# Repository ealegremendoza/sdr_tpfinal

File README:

TENSIOMETRO DIGITAL
TP Final de la materia Sistemas de Representación R1032 UTN FRBA.

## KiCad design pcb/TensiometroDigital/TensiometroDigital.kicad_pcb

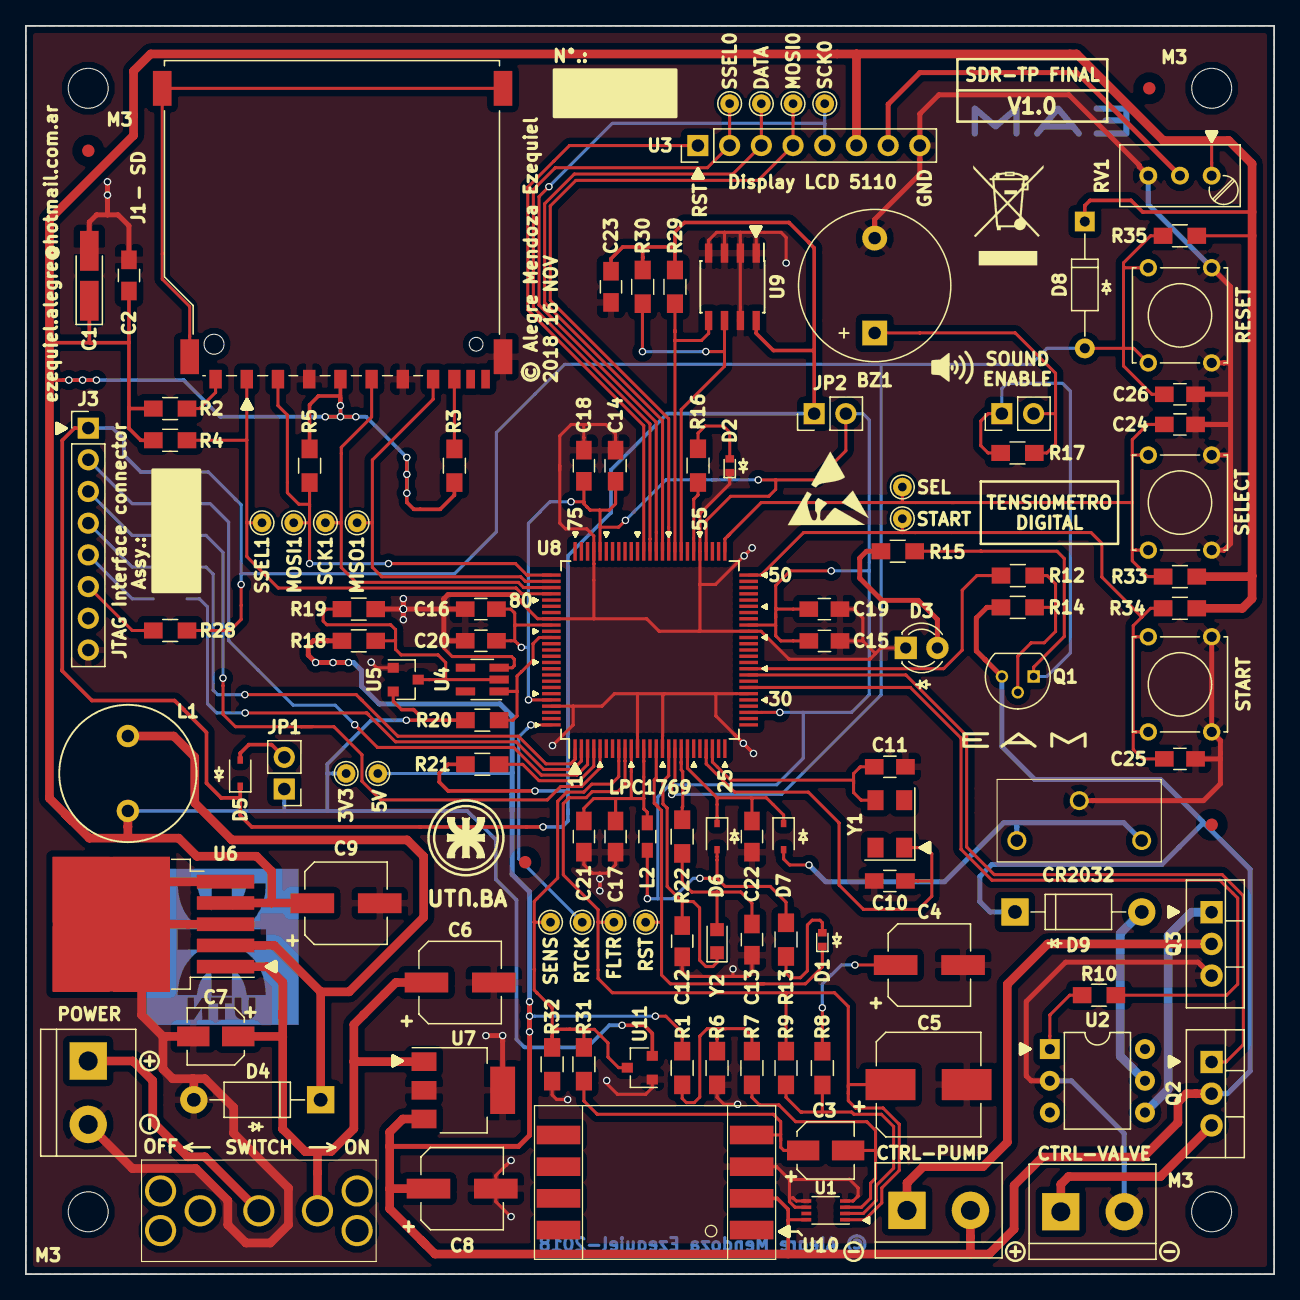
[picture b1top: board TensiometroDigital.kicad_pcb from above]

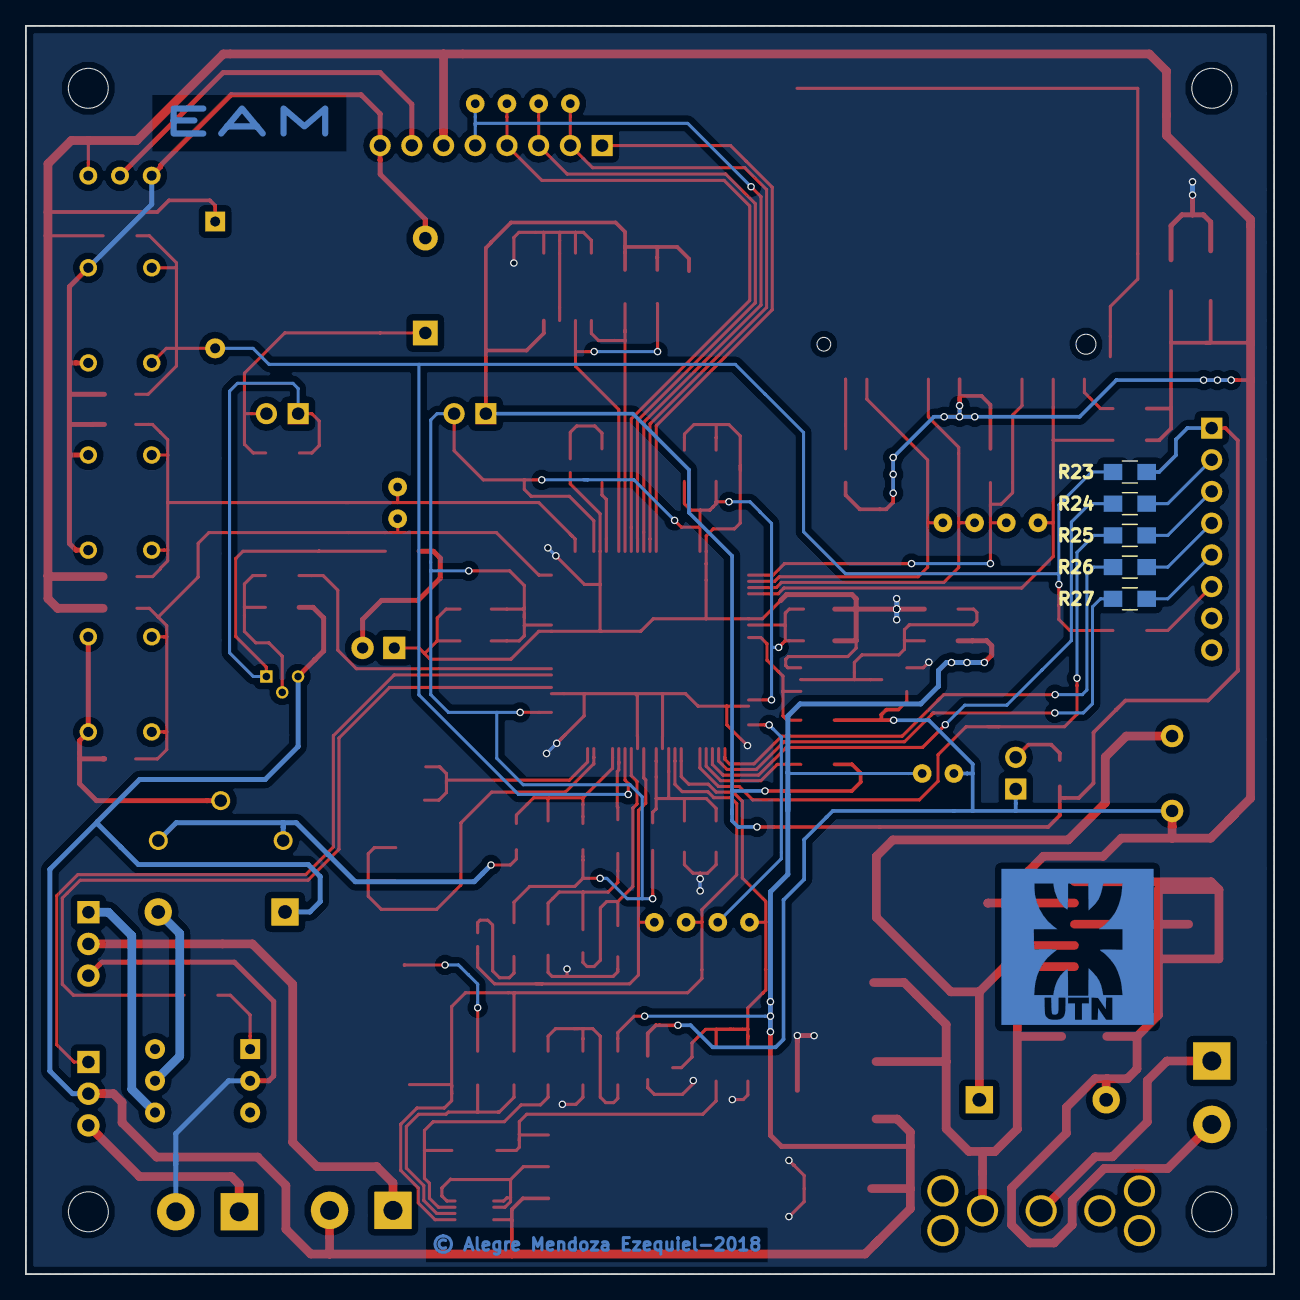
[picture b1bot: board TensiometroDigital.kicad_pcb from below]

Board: 2 copper layers, 100.0 x 100.0 mm, 126 parts (5 on the bottom side), 70 nets.

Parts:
BZ1: Buzzer-5V; Buzzer_12x9.5RM7.6
C1: 1uF x 16V; CP_Tantalum_Case-A_EIA-3216-18_Hand
C2: 100n; C_0805_HandSoldering
C3: 0.33uF; CP_Elec_4x5.7
C4: 33uF; CP_Elec_6.3x4.5
C5: 330uF; CP_Elec_8x10.5
C6: 100uF; CP_Elec_6.3x5.8
C7: 0.47uF; CP_Elec_4x5.7
C8: 47uF; CP_Elec_6.3x4.5
C9: 330uF; CP_Elec_6.3x7.7
C10, C11: 18pF; C_0805_HandSoldering
C12, C13: 5pF; C_0805_HandSoldering
C14, C15, C16, C17: 10nF; C_0805_HandSoldering
C18, C19, C20, C21, C22, C23, C24, C25, C26: 100nF; C_0805_HandSoldering
D1, D2: LED; LED_0402
D3: LED; LED_D3.0mm
D4: 1N5817; D_DO-41_SOD81_P10.16mm_Horizontal
D5: PMEG1020EA; D_SOD-323
D6, D7: 1N4448WS-7-F; D_SOD-323
D8: 1N4148; D_DO-35_SOD27_P10.16mm_Horizontal
D9: 1N4001; D_DO-41_SOD81_P10.16mm_Horizontal
F: Fiducial_1mm_Dia_2.54mm_Outer_CopperTop
F#2, F#3, F#4: Fiducial_1mm_Dia_2.54mm_Outer_CopperTop
J1: SD_Card; SD_TE_2041021_edit
J2: BAT 9V; TerminalBlock_bornier-2_P5.08mm
J3: Programacion; Socket_Strip_Straight_1x08_Pitch2.54mm
J4: VALVE; TerminalBlock_bornier-2_P5.08mm
J5: AIR PUMP; TerminalBlock_bornier-2_P5.08mm
JP1, JP2, JP3: Jumper; Socket_Strip_Straight_1x02_Pitch2.54mm
L1: 330uH; RFC1010
L2: BK1608HS220-T; L_0603_HandSoldering
M3, M3#2, M3#3, M3#4: MountingHole_3.2mm_M3
Q1: BC557; TO-92_Molded_Narrow
Q2, Q3: TIP31; TO-220-3_Vertical
R1: 24k; R_0805_HandSoldering
R2, R3, R14, R21: 10K; R_0805_HandSoldering
R4, R5, R32: 33K; R_0805_HandSoldering
R6, R33, R34: 10k; R_0805_HandSoldering
R7: 1M; R_0805_HandSoldering
R8: 1k; R_0805_HandSoldering
R9: 120k; R_0805_HandSoldering
R10: 330R; R_0805_HandSoldering
R12, R35: 4k7; R_0805_HandSoldering
R13, R16: 1k5; R_0805_HandSoldering
R15: 220R; R_0805_HandSoldering
R17, R24, R25, R26, R27, R28: 0R; R_0805_HandSoldering
R18: 1K8; R_0805_HandSoldering
R19, R29, R30: 3K3; R_0805_HandSoldering
R20: 470K; R_0805_HandSoldering
R22: 100K; R_0805_HandSoldering
R23: 12K; R_0805_HandSoldering
R31: 18k; R_0805_HandSoldering
RTC_BAT1: CR2032; CR2032_VERTICAL_HOLDER_S8401-46
RV1: 10K; Potentiometer_Trimmer_Bourns_3296W
SW2: SW_SPDT; E_SWITCH_100SP5T4B4VS2QE
SW3, SW4, SW5: SW_DPST; SW_Tactile_Straight_KSL0Axx1LFTR_edit
TP1: 5V; TestPoint_THTPad_D1.5mm_Drill0.7mm
TP2: 3V3; TestPoint_THTPad_D1.5mm_Drill0.7mm
TP3: START; TestPoint_THTPad_D1.5mm_Drill0.7mm
TP4: SEL; TestPoint_THTPad_D1.5mm_Drill0.7mm
TP5: SSEL1; TestPoint_THTPad_D1.5mm_Drill0.7mm
TP6: SCK1; TestPoint_THTPad_D1.5mm_Drill0.7mm
TP7: MISO1; TestPoint_THTPad_D1.5mm_Drill0.7mm
TP8: MOSI1; TestPoint_THTPad_D1.5mm_Drill0.7mm
TP9: SCK0; TestPoint_THTPad_D1.5mm_Drill0.7mm
TP10: SSEL0; TestPoint_THTPad_D1.5mm_Drill0.7mm
TP11: DATA; TestPoint_THTPad_D1.5mm_Drill0.7mm
TP12: MOSI0; TestPoint_THTPad_D1.5mm_Drill0.7mm
TP13: RTCK; TestPoint_THTPad_D1.5mm_Drill0.7mm
TP14: SENS; TestPoint_THTPad_D1.5mm_Drill0.7mm
TP15: FLTR; TestPoint_THTPad_D1.5mm_Drill0.7mm
TP16: RSTOUT; TestPoint_THTPad_D1.5mm_Drill0.7mm
U1: LM358; VSSOP-8_2.3x2mm_Pitch0.5mm
U2: 4N25; DIP-6_W7.62mm
U3: display_nokia5110; Socket_Strip_Straight_1x08_Pitch2.54mm
U4: LM8364BALMF20/NOPBTR-ND; SOT-23-5_HandSoldering
U5, U11: BAV199; SOT-23
U6: LM2575-3.3; TO-263-5_TabPin3
U7: LM2940-5V; SOT-223-3_TabPin2
U8: LPC1769FBD100; LQFP-100_14x14mm_P0.5mm
U9: 24LC64; SOIC-8_3.9x4.9mm_Pitch1.27mm
U10: MPXV5050GP; mpxv5050gp_case1369_01
Y1: 12MHz; Crystal_SMD_Abracon_ABM3C-4pin_5.0x3.2mm
Y2: 32.768KHz; Crystal_SMD_2012-2pin_2.0x1.2mm_HandSoldering

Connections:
+3V3: C1.1, C2.1, C9.1, D8.1, J1.4, JP1.1, L1.2, R2.1, R3.1, R4.1, R5.1, R20.1, R33.1, R34.1, R35.1, RV1.1, TP2.1, U3.6, U5.2, U6.4, U11.2
+5V: C8.1, D9.1, J5.2, Q1.3, Q2.2, R1.1, R14.1, R18.1, TP1.1, U1.8, U7.3, U10.2
/Alimentación/V+: C6.1, C7.1, SW2.1, U6.1, U7.1
/Almacenamiento/MISO: J1.7, TP7.1, U8.77
/Almacenamiento/MOSI: J1.2, R5.2, TP8.1, U8.76
/Almacenamiento/SCK: J1.5, TP6.1, U8.78
/Almacenamiento/SSEL: J1.1, R4.2, TP5.1, U8.79
/Almacenamiento/data1: J1.8, R3.2
/Almacenamiento/data2: J1.9, R2.2
/Bomba de aire/BOMBA: R10.2, U8.32
/Bomba de aire/VALVULA: Q2.1, U8.34
/Controles de usuario/~SELECT: C24.1, R33.2, SW3.1, SW3.3, TP4.1, U8.51
/Controles de usuario/~START: C25.1, R34.2, SW4.1, SW4.3, TP3.1, U8.50
/Display/CE: TP10.1, U3.2, U8.63
/Display/CLK: TP9.1, U3.5, U8.62
/Display/DATA: TP11.1, U3.3, U8.61
/Display/DIN: TP12.1, U3.4, U8.60
/Display/~RST: U3.1, U8.64
/Filtrado/IN: C3.1, R31.2, U10.4
/Indicadores/LED_BUZZER: R12.2, U8.35
/Sensor de presión/REG_OUT: R31.1, R32.1, TP14.1, U8.8, U11.3
/microcontrolador/FILTER: C5.1, R9.1, TP15.1, U1.1, U8.9
/microcontrolador/JTAG_RESETX: J3.6, R28.1
/microcontrolador/JTAG_TCLK_SWCLKX: J3.3, R25.1
/microcontrolador/JTAG_TDIX: J3.5, R27.1
/microcontrolador/JTAG_TDO_SWOX: J3.4, R26.1
/microcontrolador/JTAG_TMS_SWDIOX: J3.2, R24.1
/microcontrolador/RTCK: TP13.1, U8.100
/microcontrolador/SCL_EEPROM: R30.2, U8.58, U9.6
/microcontrolador/SDA_EEPROM: R29.2, U8.59, U9.5
/microcontrolador/STATUS_LED: R16.1, U8.56
/microcontrolador/TCLK_SWDCLK: R25.2, U8.5
/microcontrolador/TDI: R27.2, U8.2
/microcontrolador/TDO_SWO: R26.2, U8.1
/microcontrolador/TMS_SWDIO: R24.2, U8.3
/microcontrolador/VBAT: C22.1, D6.1, D7.1, U8.19
/microcontrolador/VDD_3V3: C14.1, C15.1, C16.1, C18.1, C19.1, C20.1, D6.2, JP2.2, L2.2, R13.1, U8.28, U8.42, U8.54, U8.71, U8.84, U8.96
/microcontrolador/VIO_3V3X: C23.1, D5.1, J3.1, JP2.1, R21.1, R23.1, R29.1, R30.1, U9.8
/microcontrolador/VREF: C17.1, C21.1, L2.1, U8.10, U8.12
/microcontrolador/~ARESET: R20.2, U4.1, U8.86
/microcontrolador/~MRESET: C26.1, D8.2, R23.2, R28.2, R35.2, SW5.1, SW5.3, U8.17
/microcontrolador/~RSTOUT: D1.1, TP16.1, U8.14
GND: BZ1.2, C1.2, C2.2, C4.2, C5.2, C6.2, C7.2, C8.2, C9.2, C10.2, C11.2, C12.2, C13.2, C14.2, C15.2, C16.2, C17.2, C18.2, C19.2, C20.2, C21.2, C22.2, C23.2, C24.2, C25.2, C26.2, D2.1, D3.1, D4.2, J1.3, J1.6, J1.12, J2.2, J3.8, J4.2, Q3.3, R6.2, R19.2, R32.2, RTC_BAT1.2, RV1.3, SW3.2, SW3.4, SW4.2, SW4.4, SW5.2, SW5.4, U1.4, U1.5, U1.6, U2.2, U3.8, U4.3, U5.1, U6.3, U6.5, U7.2, U8.11, U8.15, U8.31, U8.41, U8.55, U8.72, U8.83, U8.97, U9.1, U9.2, U9.3, U9.4, U9.7, U10.3, U11.1
unnamed: BZ1.1, JP3.2, R17.1
unnamed: C3.2, R7.2, U1.3
unnamed: C4.1, R8.2
unnamed: C10.1, U8.22, Y1.1
unnamed: C11.1, U8.23, Y1.2
unnamed: C12.1, U8.16, Y2.1
unnamed: C13.1, R22.2, Y2.2
unnamed: D1.2, R13.2
unnamed: D2.2, R16.2
unnamed: D3.2, R15.1
unnamed: D4.1, L1.1, U6.2
unnamed: D5.2, JP1.2
unnamed: D7.2, RTC_BAT1.1
unnamed: D9.2, U2.5
unnamed: J2.1, SW2.2
unnamed: J4.1, Q2.3
unnamed: J5.1, Q3.2
unnamed: JP3.1, Q1.1, R15.2, R17.2
unnamed: Q1.2, R12.1, R14.2
unnamed: Q3.1, U2.4
unnamed: R1.2, R6.1, R7.1
unnamed: R8.1, R9.2, U1.2
unnamed: R10.1, U2.1
unnamed: R18.2, R19.1, U4.2, U5.3
unnamed: R21.2, U8.4
unnamed: R22.1, U8.18
unnamed: RV1.2, U3.7

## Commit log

2018-08-16 inicio
2018-08-30 mirama2 update inicial
2018-09-03 pcb update
2018-09-03 pcb update 2
2018-10-18 cambios al sch
2018-11-20 Finalizado: SCH, PCB, GABINETE, DRAWINGS. FALTA: GERBERS, BOM e Informe
2018-11-20 README UPDATE
2018-11-20 Agregados GERBERS. Falta BOM e Informe
2018-11-20 Creada la BOM
2018-11-23 TP FINALIZADO. FALTA CREAR EL ZIP
2018-11-23 TP FINALIZADO. ZIP PARA ENTREGAR
2019-05-30 Proyecto terminado y entregado.
2019-05-30 readme modificado

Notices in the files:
pcb/TensiometroDigital/TensiometroDigital.kicad_pcb:
© Alegre Mendoza Ezequiel-2018
